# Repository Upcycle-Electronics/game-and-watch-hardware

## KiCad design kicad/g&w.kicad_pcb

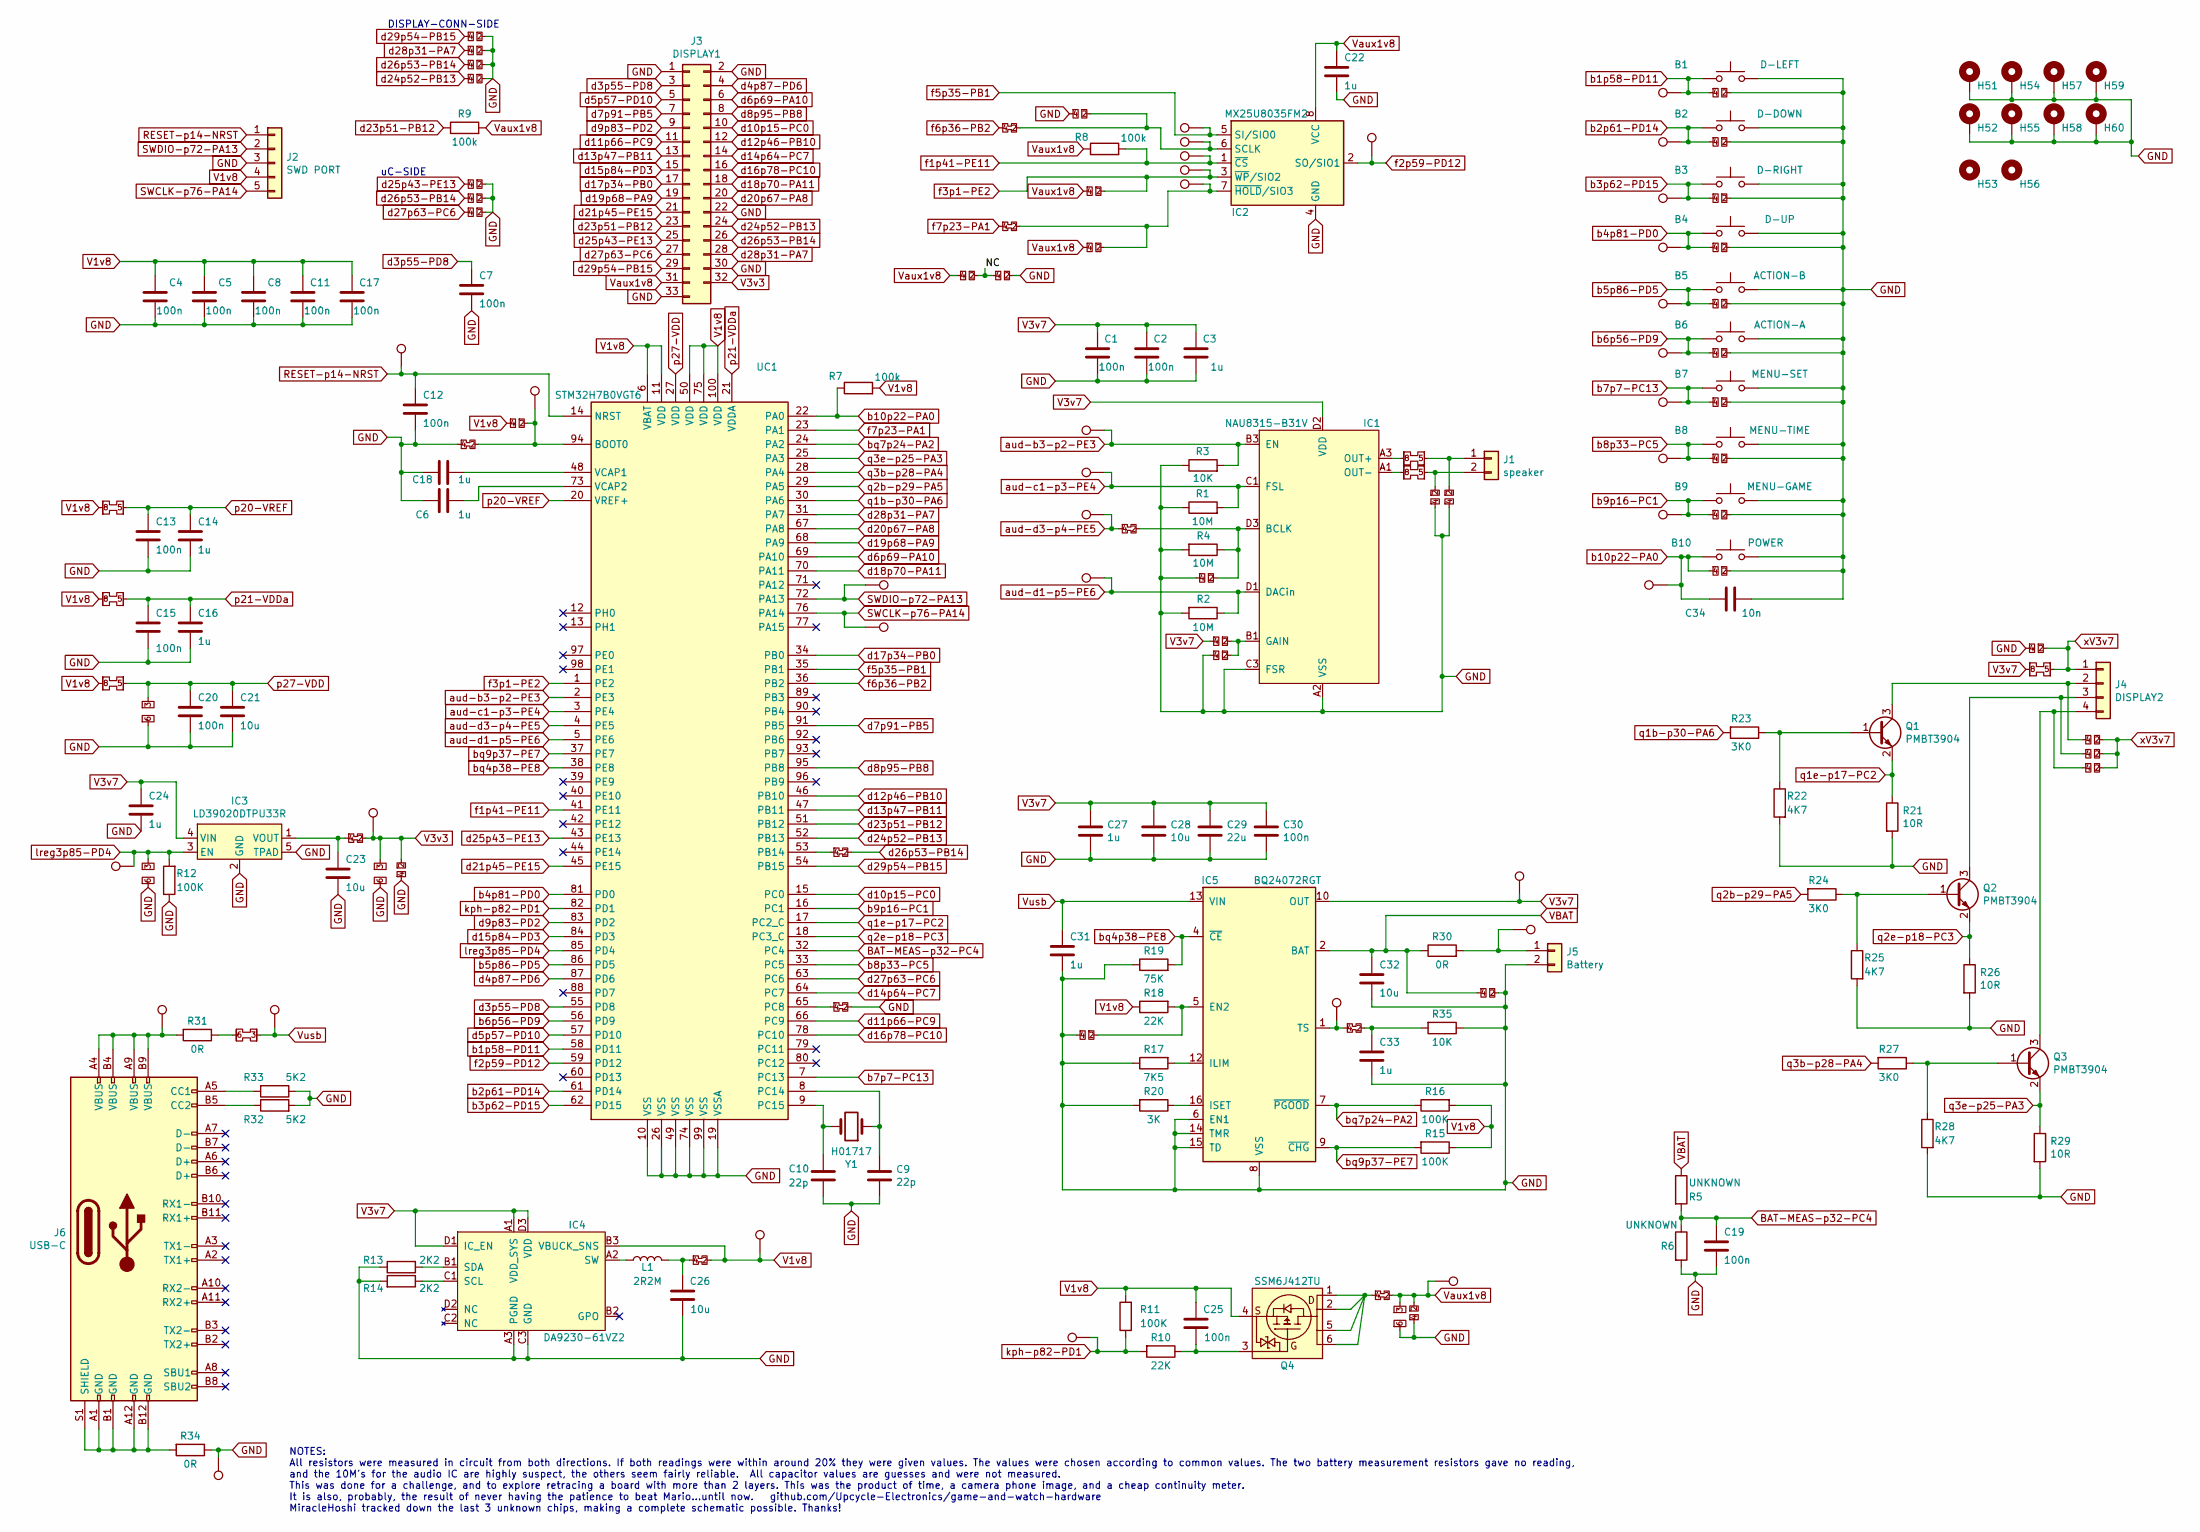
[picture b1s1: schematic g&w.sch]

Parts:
B1: D-LEFT; Button_Carbon-Contact_Round_5.00mm
B2: D-DOWN; Button_Carbon-Contact_Round_5.00mm
B3: D-RIGHT; Button_Carbon-Contact_Round_5.00mm
B4: D-UP; Button_Carbon-Contact_Round_5.00mm
B5: ACTION-B; Button_Carbon-Contact_Round_6.5mm
B6: ACTION-A; Button_Carbon-Contact_Round_6.5mm
B7: MENU-SET; Button_Carbon-Contact_Round_5.00mm
B8: MENU-TIME; Button_Carbon-Contact_Round_5.00mm
B9: MENU-GAME; Button_Carbon-Contact_Round_5.00mm
B10: POWER; SW_PUSH_1P1T_Horizontal_Nintendo_GnW
C1, C2, C4, C5, C7, C8, C11, C12, C13, C15, C17, C19, C20, C25, C30: 100n; C_0201_0603Metric
C3, C31: 1u; C_0603_1608Metric
C6, C14, C16, C18, C22, C24, C27, C33: 1u; C_0402_1005Metric
C9, C10: 22p; C_0201_0603Metric
C21, C23, C26, C28: 10u; C_0603_1608Metric
C29: 22u; C_0805_2012Metric
C32: 10u; C_0805_2012Metric
C34: 10n; C_0201_0603Metric
H51, H52, H54, H55, H57, H58, H59, H60: MountingHole_Pad; MountingHole_2.0mm
H53: MountingHole; MountingSlot_NC_1.3x2.2mm
H56: MountingHole; MountingHole_NC_1.5mm
IC1: NAU8315-B31V; WLCSP-12_1.18x1.95_Layout3x4_P0.4mm
IC2: MX25U8035FM2; SOP-8_5.28x5.23mm_P1.27mm
IC3: LD39020DTPU33R; DFN-4-1EP_1x1_P0.65mm_EP0.56x0.56mm
IC4: DA9230-61VZ2; WLCSP-12_1.28x1.68_Layout3x4_P0.4mm
IC5: BQ24072RGT; VQFN-16-1EP_3x3mm_P0.5mm_EP1.6x1.6mm
J1: speaker; Speaker
J2: SWD PORT; PinHeader_1x05_P1.27mm_Vertical
J3: DISPLAY1; Molex_502078-3310_2Rows-33Pins-1MP_P0.5mm-int0.25mm_Horizon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
J4: DISPLAY2; Molex_Easy-On_503480-0400_1x04-1MP_P1.00mm_Horizontal
J5: Battery; Molex_Pico-EZmate_78171-0002_1x02-1MP_P1.20mm_Vertical
J6: USB-C; USB_C_Receptacle_JAE_DX07BN24JA2
JP51, JP52, JP53, JP83, JP84, JP102: jmp-0805; JMP-0805-CLOSED
JP54, JP55, JP58, JP89: JMP-0603-OPEN; R_0603_1608Metric
JP56: JMP-0603-CLOSED
JP57, JP67, JP69, JP70, JP72, JP73, JP77, JP82, JP85, JP88: JMP-0402-CLOSED
JP59, JP60, JP61, JP62, JP63, JP64, JP65, JP66, JP68, JP71, JP74, JP75, JP76, JP78, JP79, JP80, JP81, JP86, JP87, JP90, JP91, JP92, JP93, JP94, JP95, JP96, JP97, JP98, JP99, JP100, JP101, JP103, JP104, JP105, JP106, JP107: JMP-0402-OPEN; R_0402_1005Metric
L1: 2R2M; L_0806_2016Metric
Q1, Q2, Q3: PMBT3904; SOT-23
Q4: SSM6J412TU; Toshiba_UF6_SOT363F
R1, R2, R4: 10M; R_0201_0603Metric
R3, R35: 10K; R_0201_0603Metric
R5, R6: UNKNOWN; R_0201_0603Metric
R7, R8, R9: 100k; R_0201_0603Metric
R10, R18: 22K; R_0201_0603Metric
R11, R12, R15, R16: 100K; R_0201_0603Metric
R13, R14: 2K2; R_0201_0603Metric
R17: 7K5; R_0201_0603Metric
R19: 75K; R_0201_0603Metric
R20: 3K; R_0201_0603Metric
R21, R26, R29: 10R; R_0201_0603Metric
R22, R25, R28: 4K7; R_0201_0603Metric
R23, R24, R27: 3K0; R_0201_0603Metric
R30, R31: 0R; R_0402_1005Metric
R32, R33: 5K2; R_0201_0603Metric
R34: 0R; R_0603_1608Metric
TP51, TP52, TP53, TP54, TP55, TP56, TP57, TP58, TP59, TP60, TP61, TP62, TP63, TP64, TP65, TP66, TP67, TP68, TP69, TP70, TP71, TP72, TP73, TP74, TP75, TP76, TP77, TP78, TP79, TP80, TP81, TP82, TP83, TP84, TP85: TestPoint; gnw-TestPoint_Pad_D1.0mm
UC1: STM32H7B0VGT6; LQFP-100_14x14mm_P0.5mm
Y1: H01717; Crystal_SMD_3215-2Pin_3.2x1.5mm

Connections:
/NC: JP106.2, JP107.1
BAT-MEAS-p32-PC4: C19.1, R5.2, R6.1, UC1.32 (PC4)
unnamed: C6.2, UC1.73 (VCAP2)
unnamed: C9.1, UC1.8 (PC14), Y1.1
unnamed: C10.1, UC1.9 (PC15), Y1.2
unnamed: C18.1, UC1.48 (VCAP1)
unnamed: C23.1, IC3.1 (VOUT), JP57.1
unnamed: C25.1, Q4.3, R10.1
unnamed: C26.1, JP82.1, L1.2
unnamed: C33.1, JP88.2, R35.2
unnamed: IC1.A1 (OUT-), JP84.1
unnamed: IC1.A3 (OUT+), JP83.1
unnamed: IC1.B1 (GAIN), JP79.2, JP80.2
unnamed: IC1.D3 (BCLK), JP77.2, JP78.2, R4.1
unnamed: IC2.6 (SCLK), JP72.2, JP74.2, TP63.1
unnamed: IC2.7 (~HOLD~/SIO3), JP73.2, JP76.2, TP66.1
unnamed: IC4.A2 (SW), L1.1
unnamed: IC4.B1 (SDA), R13.2
unnamed: IC4.C1 (SCL), R14.1
unnamed: IC5.1 (TS), JP88.1, TP68.1
unnamed: IC5.5 (EN2), JP71.2, R18.2
unnamed: IC5.12 (ILIM), R17.2
unnamed: IC5.16 (ISET), R20.1
unnamed: J1.1, JP83.2, JP87.2
unnamed: J1.2, JP84.2, JP86.2
unnamed: J4.2, JP103.1, Q1.3 (C)
unnamed: J4.3, JP104.1, Q2.3 (C)
unnamed: J4.4, JP105.1, Q3.3 (C)
unnamed: J5.1, R30.2, TP70.1
unnamed: J6.A4 (VBUS), J6.A9 (VBUS), J6.B4 (VBUS), J6.B9 (VBUS), R31.2, TP52.1
unnamed: J6.A5 (CC1), R33.2
unnamed: J6.B5 (CC2), R32.1
unnamed: JP56.1, R31.1
unnamed: JP67.2, JP68.2, TP56.1, UC1.94 (BOOT0)
unnamed: JP69.1, UC1.53 (PB14)
unnamed: JP70.1, UC1.65 (PC8)
unnamed: JP85.1, Q4.1, Q4.2, Q4.5, Q4.6
unnamed: Q1.1 (B), R22.1, R23.1
unnamed: Q2.1 (B), R24.1, R25.1
unnamed: Q3.1 (B), R27.1, R28.1
RESET-p14-NRST: C12.1, J2.1, TP81.1, UC1.14 (NRST)
SWCLK-p76-PA14: J2.5, TP83.1, UC1.76 (PA14)
SWDIO-p72-PA13: J2.2, TP82.1, UC1.72 (PA13)
V1v8: C4.1, C5.1, C8.1, C11.1, C17.1, C25.2, IC4.B3 (VBUCK_SNS), J2.4, JP51.1, JP52.1, JP53.1, JP68.1, JP82.2, Q4.4, R7.2, R11.2, R15.1, R16.2, R18.1, TP84.1, UC1.6 (VBAT), UC1.11 (VDD), UC1.50 (VDD), UC1.75 (VDD), UC1.100 (VDD)
V3v3: J3.32, JP57.2, JP58.2, JP59.2, TP55.1
V3v7: C1.1, C2.1, C3.1, C24.1, C27.1, C28.1, C29.1, C30.1, IC1.B2 (VDD), IC1.C2 (VDD), IC1.D2 (VDD), IC3.4 (VIN), IC4.A1 (VDD_SYS), IC4.D1 (IC_EN), IC4.D3 (VDD), IC5.10 (OUT), IC5.11 (OUT), JP80.1, JP102.1, TP85.1
VBAT: C32.1, IC5.2 (BAT), IC5.3 (BAT), JP81.1, R5.1, R30.1
Vaux1v8: C22.1, IC2.8 (VCC), J3.31, JP75.1, JP76.1, JP85.2, JP89.2, JP90.2, JP106.1, R8.1, R9.2, TP69.1
Vusb: C31.1, IC5.13 (VIN), JP56.2, TP54.1
aud-b3-p2-PE3: IC1.B3 (EN), R3.2, TP60.1, UC1.2 (PE3)
aud-c1-p3-PE4: IC1.C1 (FSL), R1.2, TP58.1, UC1.3 (PE4)
aud-d1-p5-PE6: IC1.D1 (DACin), R2.1, TP57.1, UC1.5 (PE6)
aud-d3-p4-PE5: JP77.1, TP59.1, UC1.4 (PE5)
b1p58-PD11: B1.1, JP91.1, TP72.1, UC1.58 (PD11)
b2p61-PD14: B2.1, JP92.1, TP73.1, UC1.61 (PD14)
b3p62-PD15: B3.1, JP93.1, TP74.1, UC1.62 (PD15)
b4p81-PD0: B4.1, JP94.1, TP75.1, UC1.81 (PD0)
b5p86-PD5: B5.1, JP95.1, TP76.1, UC1.86 (PD5)
b6p56-PD9: B6.1, JP96.1, TP77.1, UC1.56 (PD9)
b7p7-PC13: B7.1, JP97.1, TP78.1, UC1.7 (PC13)
b8p33-PC5: B8.1, JP98.1, TP79.1, UC1.33 (PC5)
b9p16-PC1: B9.1, JP99.1, TP80.1, UC1.16 (PC1)
b10p22-PA0: B10.2, C34.1, JP100.1, R7.1, TP71.1, UC1.22 (PA0)
bq4p38-PE8: IC5.4 (~CE), R19.2, UC1.38 (PE8)
bq7p24-PA2: IC5.7 (~PGOOD), R16.1, UC1.24 (PA2)
bq9p37-PE7: IC5.9 (~CHG), R15.2, UC1.37 (PE7)
d3p55-PD8: C7.1, J3.3, UC1.55 (PD8)
d4p87-PD6: J3.4, UC1.87 (PD6)
d5p57-PD10: J3.5, UC1.57 (PD10)
d6p69-PA10: J3.6, UC1.69 (PA10)
d7p91-PB5: J3.7, UC1.91 (PB5)
d8p95-PB8: J3.8, UC1.95 (PB8)
d9p83-PD2: J3.9, UC1.83 (PD2)
d10p15-PC0: J3.10, UC1.15 (PC0)
d11p66-PC9: J3.11, UC1.66 (PC9)
d12p46-PB10: J3.12, UC1.46 (PB10)
d13p47-PB11: J3.13, UC1.47 (PB11)
d14p64-PC7: J3.14, UC1.64 (PC7)
d15p84-PD3: J3.15, UC1.84 (PD3)
d16p78-PC10: J3.16, UC1.78 (PC10)
d17p34-PB0: J3.17, UC1.34 (PB0)
d18p70-PA11: J3.18, UC1.70 (PA11)
d19p68-PA9: J3.19, UC1.68 (PA9)
d20p67-PA8: J3.20, UC1.67 (PA8)
d21p45-PE15: J3.21, UC1.45 (PE15)
d23p51-PB12: J3.23, R9.1, UC1.51 (PB12)
d24p52-PB13: J3.24, JP63.1, UC1.52 (PB13)
d25p43-PE13: J3.25, JP64.1, UC1.43 (PE13)
d26p53-PB14: J3.26, JP62.1, JP65.1, JP69.2
d27p63-PC6: J3.27, JP66.1, UC1.63 (PC6)
d28p31-PA7: J3.28, JP61.1, UC1.31 (PA7)
d29p54-PB15: J3.29, JP60.1, UC1.54 (PB15)
f1p41-PE11: IC2.1 (~CS), R8.2, TP64.1, UC1.41 (PE11)
f2p59-PD12: IC2.2 (SO/SIO1), TP67.1, UC1.59 (PD12)
f3p1-PE2: IC2.3 (~WP~/SIO2), JP75.2, TP65.1, UC1.1 (PE2)
f5p35-PB1: IC2.5 (SI/SIO0), TP62.1, UC1.35 (PB1)
f6p36-PB2: JP72.1, UC1.36 (PB2)
f7p23-PA1: JP73.1, UC1.23 (PA1)
kph-p82-PD1: R10.2, R11.1, TP61.1, UC1.82 (PD1)
lreg3p85-PD4: IC3.3 (EN), JP55.2, R12.2, TP51.1, UC1.85 (PD4)
p20-VREF: C13.1, C14.1, JP51.2, UC1.20 (VREF+)
p21-VDDa: C15.1, C16.1, JP52.2, UC1.21 (VDDA)
p27-VDD: C20.1, C21.1, JP53.2, JP54.2, UC1.27 (VDD)
q1b-p30-PA6: R23.2, UC1.30 (PA6)
q1e-p17-PC2: Q1.2 (E), R21.1, UC1.17 (PC2_C)
q2b-p29-PA5: R24.2, UC1.29 (PA5)
q2e-p18-PC3: Q2.2 (E), R26.1, UC1.18 (PC3_C)
q3b-p28-PA4: R27.2, UC1.28 (PA4)
q3e-p25-PA3: Q3.2 (E), R29.1, UC1.25 (PA3)
xV3v7: J4.1, JP101.2, JP102.2, JP103.2, JP104.2, JP105.2

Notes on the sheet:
uC-SIDE
DISPLAY-CONN-SIDE
NOTES: All resistors were measured in circuit from both directions. If both readings were within around 20% they were given values. The values were chosen according to common values. The two battery measurement resistors gave no reading, and the 10M's for the audio IC are highly suspect, the others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

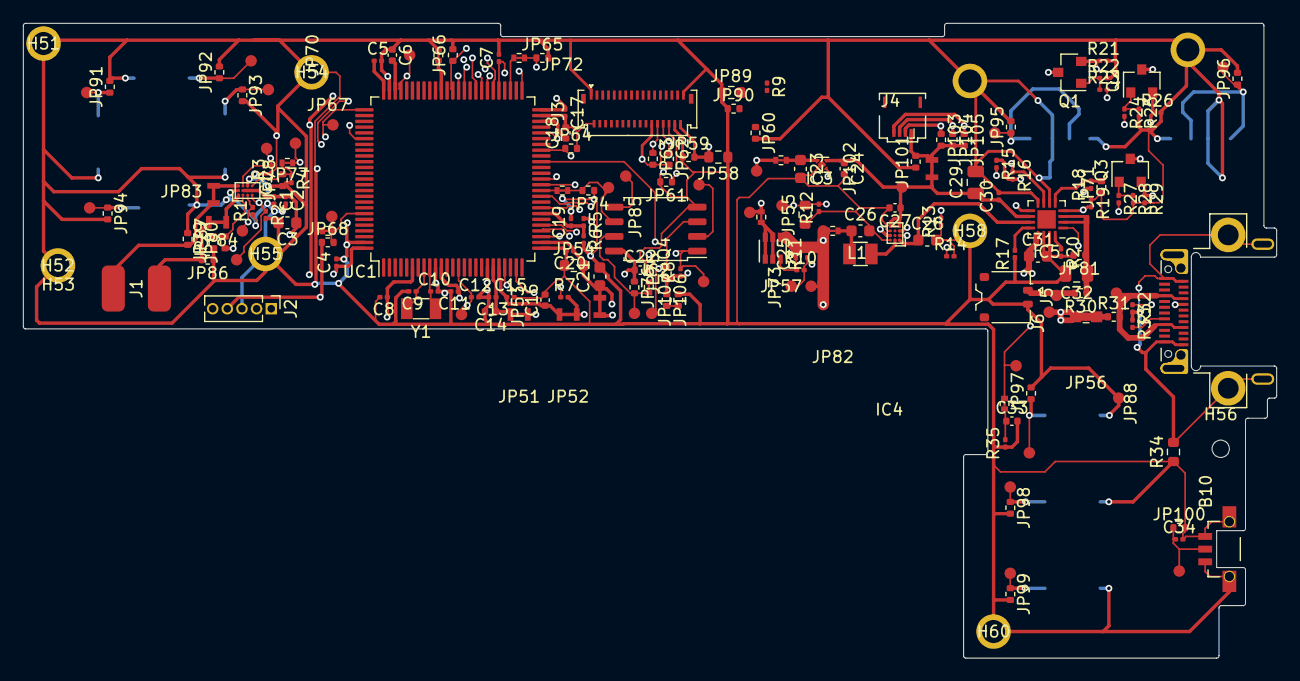
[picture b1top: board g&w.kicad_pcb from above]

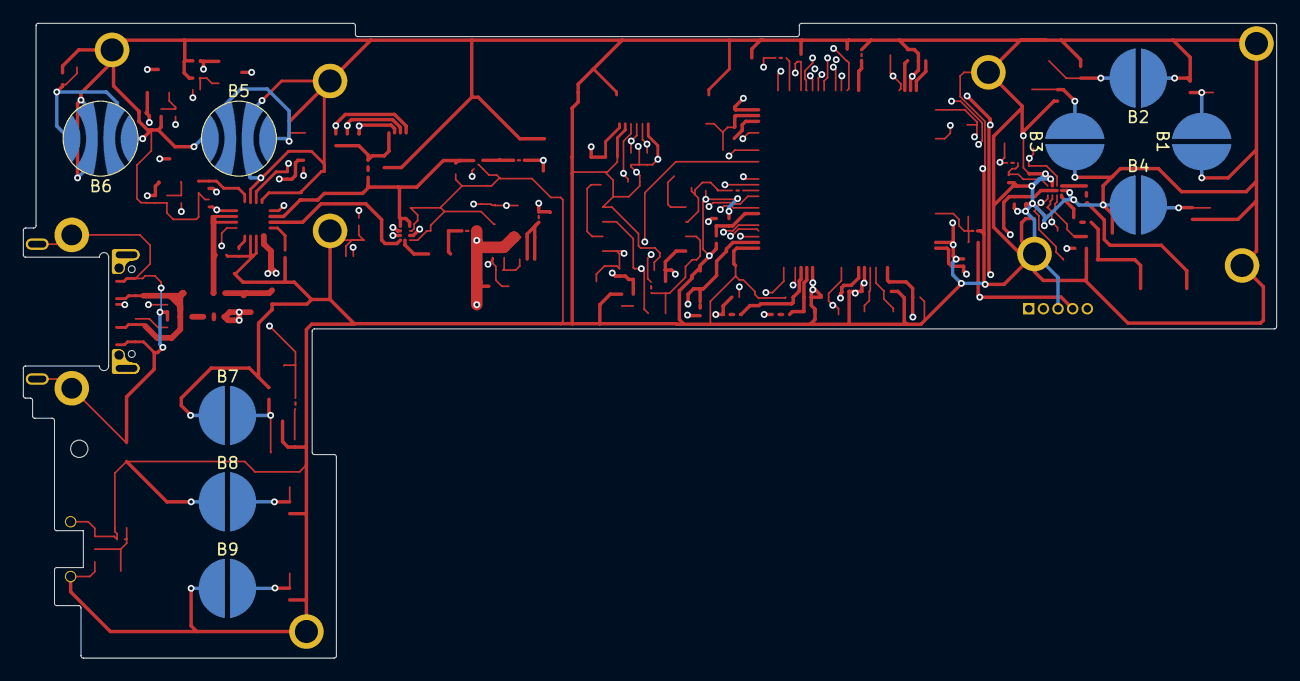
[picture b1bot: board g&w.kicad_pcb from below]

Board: 4 copper layers, 108.7 x 55.1 mm, 199 parts (9 on the bottom side), 112 nets.

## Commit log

2020-12-01 begin
2020-12-02 gimp-trace1
2020-12-02 progress
2020-12-04 final draft
2020-12-05 xrays are fun
2020-12-07 Retrace Version 1.0 and spreadsheet pin maps started
2020-12-07 image
2020-12-09 Version 1v1
2020-12-09 Version 1v11 fix USB pin connection
2020-12-09 the unwelcome art department
2020-12-10 schematic progress
2020-12-11 Version 1.12
2020-12-12 Version 1.13/designators for R/C's and in-circuit R-meas-vals/kicad0v2
2020-12-13 4 footprints left to create b4 layout begins
2020-12-15 trace 1v14/Schematic 1v0/layout begins
2020-12-16 kicad board outline
2020-12-17 tweak footprints, setup design rules for 4 layers at common proto board house and refine board outline
2020-12-17 wanted
2020-12-19 datasheets for ICBOM
2020-12-20 Updated Trace&Schematic with new parts numbers. Made new footprints for both BGA's and 3v3 reg. Still need to revise USB-C connector footprint.
2020-12-21 USB-C footprint updated from datasheet drawing 1:1 with critical dimensions layer in PCBnew
2020-12-22 all footprints placed, a very rough dxf graphics layer was made to locate most components, several footprints were tweaked and a few missing from the schematic were added and will be in the next revi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
2020-12-23 about 1/3rd routed
2020-12-25 first draft: full retrace of interior traces and ground plane. Also the board is designed for 3 layers, No routing conflicts found.
2020-12-26 Color xrays are...busy. Needs more polish, but Trace 2v0 is here.
2020-12-29 almost done
2020-12-31 progress img
2021-01-03 Trace 3v0
2021-01-03 Trace 3.0
2021-01-04 Trace 3v1/Schematic1v2/Pinmap remade in Inkscape (SVG included in current version folder)
2021-01-05 Trace 3v2 and compilation pdf
2021-01-05 git push is the best way to improve error detection

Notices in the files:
kicad/g&w.sch:
Licensed under the MIT License.
Copyright (c) 2020 Jake Little
